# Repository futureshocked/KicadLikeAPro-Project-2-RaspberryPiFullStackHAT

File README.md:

# Kicad Like A Pro - Project 2 - Raspberry Pi Full Stack HAT
This repository contains the PCB design project from the book and course "[Kicad Like a Pro](https://techexplorations.com/so/kicada/)"

In this project you will build on the knowledge and skill of the previous two project and design an Arduino-compatible board using, mostly, surface-mounted components. 

The board will contain a micro controller, two EEPROM modules, a clock and calendar module, two crystal oscillators, and several SMD-sized resistors, capacitors and LEDs. In addition, it will include headers for connecting peripherals to the micro controller.

All this, in a relatively small board, measuring 44x28 mm. Working on this board will give you the opportunity to explore some of Kicad’s powerful features, such as splitting schematic diagrams into more than one sheets, using an external autorouter, and converting a two-layer board into a four layer board.

The name I have given to this board is “Battery powered Arduino with clock and extended EEPROM”. Or, let’s call it “BACEE”, for short.

Please go to techexplorations.com for more information about this book and other Tech Explorations courses and projects.

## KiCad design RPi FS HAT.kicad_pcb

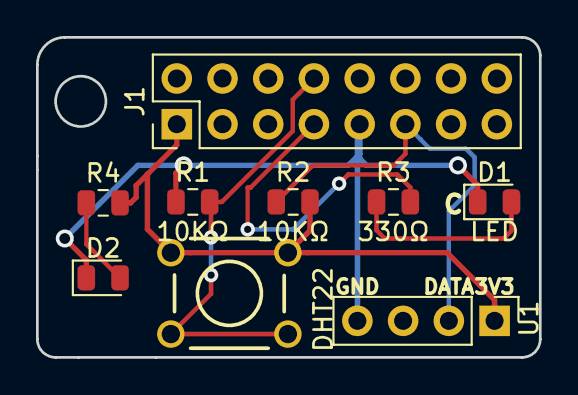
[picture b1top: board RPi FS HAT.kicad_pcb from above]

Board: 2 copper layers, 27.9 x 17.8 mm, 9 parts (0 on the bottom side), 7 nets.

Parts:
D1, D2: LED; LED_0805_2012Metric
J1: Raspberry_Pi_2_3; PinHeader_2x08_P2.54mm_Vertical
R1, R2: 10KΩ; R_0805_2012Metric
R3, R4: 330Ω; R_0805_2012Metric
SW1: SW_DPST; SW_PUSHBUTTON_PTH
U1: DHT22; PinHeader_1x04_P2.54mm_Vertical

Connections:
/3V3: J1.1, R2.2, R4.2, SW1.1, U1.1
/button_input: J1.8, R1.2, SW1.2
/led: J1.7, R3.2
/sensor_data: J1.11, R2.1, U1.2
GND: D1.1, D2.1, J1.6, J1.9, R1.1, U1.4
unnamed: D1.2, R3.1
unnamed: D2.2, R4.1

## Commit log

2018-08-17 New project started, added symbols in Eeschema.
2018-08-17 Symbol placement complete.
2018-08-17 Association completed.
2018-08-17 Updated symbol arrangement, done with wiring.
2018-08-17 Added PWR_FLG and Unconnected.
2018-08-17 Replaced GND wires with GND symbol.
2018-08-17 Replaced wires with net labels .
2018-08-17 Named last few wires.
2018-08-17 Extended a wire for clarity.
2018-08-17 Extended a wire for clarity #2.
2018-08-17 Added comments.
2018-08-17 Created netlist file.
2018-08-17 Imported netlist and set design ruled.
2018-08-17 Header and hole in place.
2018-08-17 Outline with rounded corners.
2018-08-17 Footprints placed.
2018-08-17 Completed placement.
2018-08-17 Drawn tracks.
2018-08-17 Added back copper fill.
2018-08-17 Added text silkscreen pabels to the front.
2018-08-18 Added Gerbers, completed project.
2018-08-28 Added new symbols.
2018-08-28 New netlist file contains a second LED and resistor.
2018-08-28 Completed update of the board.
2018-09-17 Added non-class letter N for fenced in areas.
